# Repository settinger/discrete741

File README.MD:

# MD741, a dis-integrated circuit

## A 741-style op-amp made of discrete components, DIP-8 size

This is a challenge posted by [Albert van Dalen](https://hackaday.io/project/177194-discrete-741-operational-amplifier-in-dil8) that is extremely silly (so, ideal for me). So, Evil Mad Scientist Labs famously [scaled up the old μA741 op-amp](https://shop.evilmadscientist.com/productsmenu/762), splitting it into discrete parts. Can it be scaled back down to DIP-8 size, but keeping the discrete parts?

More info on [Albert's personal site](https://www.avdweb.nl/div/misc2/discrete-741-operational-amplifier-in-dil8). I had to adapt the challenge a little bit; I found the SOT-723 transistors were still too big, so I switched to BJTs in the SOT-883L package (1.0mm by 0.6mm, a wee bit wider than an 0402 component). There are probably some more space savings to be gained by finding a cleverer part arrangement and by switching from KiCad's 0201 footprint to a more compact 0201 footprint.

Evil Mad Scientist Labs has a large 555 timer kit, also. It seemed only natural to tackle that one, too! [My approach to that challenge is here](https://github.com/settinger/discrete555).

TODO: Re-check design, order boards and parts if I'm feeling brave, order stencil if I'm not feeling _that_ brave, figure out how I'm going to power a ±15V op-amp without access to a benchtop power supply.

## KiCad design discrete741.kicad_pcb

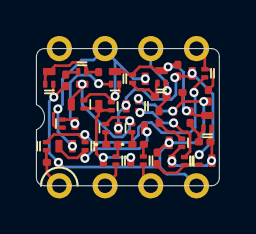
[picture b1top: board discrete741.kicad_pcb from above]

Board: 2 copper layers, 10.2 x 7.6 mm, 35 parts (0 on the bottom side), 26 nets.

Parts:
C1: 33pF; C_0201_0603Metric
D1, D2: D_Schottky; D_0201_0603Metric
J1: DIP-8 Pins; DIP-8_W7.62mm
Q1, Q2, Q5, Q6, Q7, Q10, Q11, Q14, Q15, Q16, Q17, Q18, Q22: CET3904E; SOT-883L-alt
Q3, Q4, Q8, Q9, Q12, Q13, Q20: CET3906E; SOT-883L
R1, R2: 1kΩ; R_0201_0603Metric
R3, R12: 51kΩ; R_0201_0603Metric
R4, R7: 4.7kΩ; R_0201_0603Metric
R5: 39kΩ; R_0201_0603Metric
R8: 7.5kΩ; R_0201_0603Metric
R9: 24Ω; R_0201_0603Metric
R10, R11: 51Ω; R_0201_0603Metric

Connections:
In+: J1.3, Q1.1
In-: J1.2, Q2.1
unnamed: C1.1, Q13.3, Q14.1, Q15.3, Q18.3, R7.1
unnamed: C1.2, Q4.3, Q6.3, Q16.1, Q22.3
unnamed: D1.1, Q3.2
unnamed: D1.2, Q1.2
unnamed: D2.1, Q4.2
unnamed: D2.2, Q2.2
unnamed: Q1.3, Q2.3, Q8.1, Q8.3, Q9.1
unnamed: Q3.3, Q5.3, Q7.1
unnamed: Q5.1, Q6.1, Q7.2, R3.1
unnamed: Q10.1, Q11.1, Q11.3, R5.2
unnamed: Q10.2, R4.1
unnamed: Q3.1, Q4.1, Q9.3, Q10.3
unnamed: Q12.1, Q12.3, Q13.1, R5.1
unnamed: Q14.2, Q15.1, R9.1
unnamed: Q16.2, Q17.1, R12.1
unnamed: Q16.3, Q17.3, Q18.2, Q20.1, R8.2
unnamed: Q17.2, Q22.1, R11.1
unnamed: Q18.1, R7.2, R8.1
unnamed: Q20.2, R10.2
Offset1: J1.1, Q5.2, R1.1
Offset2: J1.5, Q6.2, R2.1
Output: J1.6, Q15.2, R9.2, R10.1
Vcc+: J1.7, Q7.3, Q8.2, Q9.2, Q12.2, Q13.2, Q14.3
Vcc-: J1.4, Q11.2, Q20.3, Q22.2, R1.2, R2.2, R3.2, R4.2, R11.2, R12.2

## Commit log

2021-10-02 Init commit
2021-10-02 links in readme
2021-10-02 cosmetic changes
2021-10-02 Readme edits
2021-10-02 Added mark to distinguish NPN and PNP BJTs
2021-10-12 Added diodes per latest version of EMSL kit
2021-10-12 Update graphics
